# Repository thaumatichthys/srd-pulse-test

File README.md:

# Step Recovery Diode Pulse Generator

Note this thing hasn't been tested yet so all of this could just be stuff I dreamed up and might not work at all.

Unfortunately there seems to be only one step recovery diode (SRD) that is easily obtainable nowadays on Digikey or mouser. That being the MACOM MA144769-287T. 
This one is pretty mediocre compared to the high performance ones used in sampling heads etc, with a transition time of 150ps, around 1pF of capacitance, and it is a SOT-23 package which 
is pretty large and has a correspondingly huge package inductance. Therefore the performance of this pulse generator is not expected to be too crazy. Hopefully I can get sub 300ps pulses with
dv/dt of greater than maybe 10-20 mV/ps rise and fall time.

### SRD Drive

To get an SRD to "snap", you basically just run a forward current through it for a while, and it will build up an internal stored charge with the rate proportional to the amount of charge it has 
already. After it has a forward current running and some stored charge, you basically try to feed as much reverse current as possible, and it will basically start conducting using that stored charge.
After that runs out, it will abruptly stop conducting, and this impedance step is where the pulse comes from. This board uses the EPC21601 GaN eToF laser driver to do this. The EPC21601 seems to be pretty
good for this since it advertises <1ns fall time and was actually designed with timing accuracy in mind, unlike devices made for switching power supplies. It also has a gate driver built in and comes in a small
(read low inductance) package. Unfortunately that makes it kind of painful to assemble by hand.

### Stub Pulse Generator

The SRD circuit makes kind of a pulse with a fast rising edge and a slow RC-like falling edge. To speed up the falling edge, this board uses a ~16mm shorted 50 ohm stub. When the step forms, it goes down both the stub and towards the output, but the stub path has a reflection coefficient of gamma = -1, so the reflection will be negative. This negative reflection sums to hopefully close to zero, so the output will have a fast fall time too. This should all add together to roughly a 200-300ps pulse.

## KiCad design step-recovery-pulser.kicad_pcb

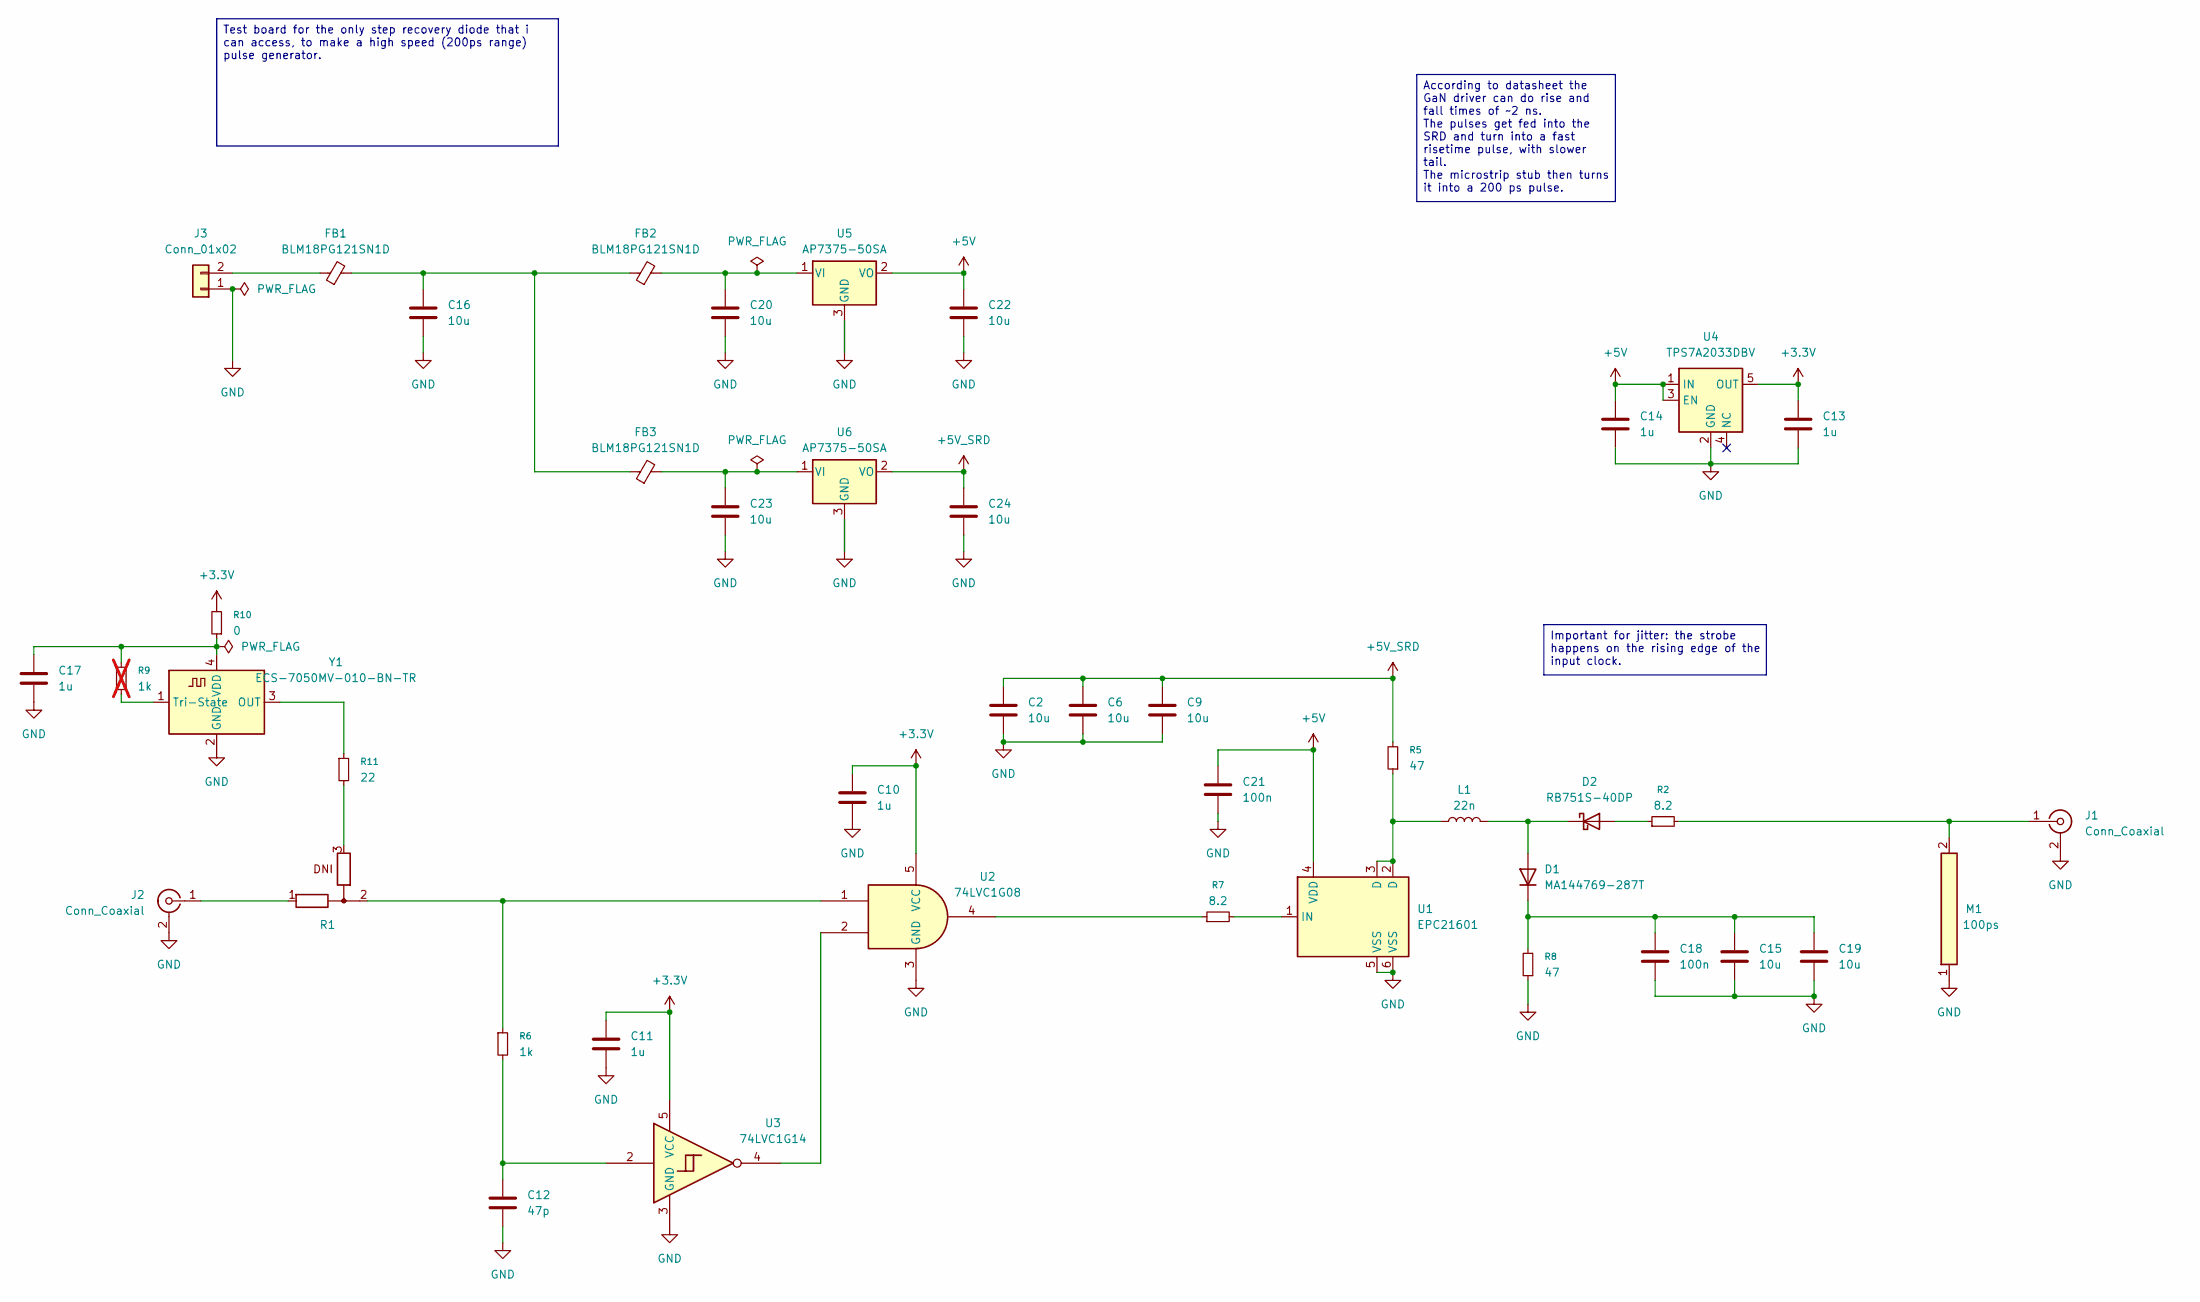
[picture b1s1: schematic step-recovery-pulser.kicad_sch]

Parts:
C2, C6, C9, C15, C16, C19, C20, C22, C23, C24: 10u; C_0805_2012Metric
C10, C11, C13, C14, C17: 1u; C_0402_1005Metric
C12: 47p; C_0402_1005Metric
C18, C21: 100n; C_0201_0603Metric
D1: MA144769-287T; SOT-23
D2: RB751S-40DP; D_0201_0603Metric
FB1, FB2, FB3: BLM18PG121SN1D; L_0603_1608Metric
J1, J2: Conn_Coaxial; ADAMTECH_RF2-143-T-17-50-G_IMPROVED
J3: Conn_01x02; PinHeader_1x02_P2.54mm_Vertical
L1: 22n; L_0402_1005Metric
M1: 100ps; MICROSTRIP_L17_W0.35
R1: R_0402_SELECT_MIRRORED
R2, R7: 8.2; R_0201_0603Metric
R5, R8: 47; R_0805_2012Metric
R6: 1k; R_0402_1005Metric
R9: 1k; R_0402_1005Metric; not fitted
R10: 0; R_0402_1005Metric
R11: 22; R_0402_1005Metric
U1: EPC21601; EPC_BGA-6_P0.5
U2: 74LVC1G08; SOT-353_SC-70-5
U3: 74LVC1G14; SOT-353_SC-70-5
U4: TPS7A2033DBV; SOT-23-5
U5, U6: AP7375-50SA; SOT-23
Y1: ECS-7050MV-010-BN-TR; Oscillator_SMD_IQD_IQXO70-4Pin_7.5x5.0mm_HandSoldering

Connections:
+3.3V: C10.1, C11.1, C13.1, R10.2, U2.5 (VCC), U3.5 (VCC), U4.5 (OUT)
+5V: C14.1, C21.1, C22.2, U1.4 (VDD), U4.1 (IN), U4.3 (EN), U5.2 (VO)
+5V_SRD: C2.2, C6.2, C9.2, C24.2, R5.2, U6.2 (VO)
GND: C2.1, C6.1, C9.1, C10.2, C11.2, C12.1, C13.2, C14.2, C15.1, C16.1, C17.2, C18.2, C19.1, C20.1, C21.2, C22.1, C23.1, C24.1, J1.2 (Ext), J2.2 (Ext), J3.1, M1.1, R8.1, U1.5 (VSS), U1.6 (VSS), U2.3 (GND), U3.3 (GND), U4.2 (GND), U5.3 (GND), U6.3 (GND), Y1.2 (GND)
unnamed: C12.2, R6.2, U3.2
unnamed: C16.2, FB1.2, FB2.1, FB3.1
unnamed: D1.1 (A), D2.1 (K), L1.2
unnamed: C15.2, C18.1, C19.2, D1.3 (K), R8.2
unnamed: D2.2 (A), R2.1
unnamed: J1.1 (In), M1.2, R2.2
unnamed: J2.1 (In), R1.1
unnamed: FB1.1, J3.2
unnamed: L1.1, R5.1, U1.2 (D), U1.3 (D)
unnamed: R1.2, R6.1, U2.1
unnamed: R1.3, R11.2
unnamed: R7.1, U2.4
unnamed: R7.2, U1.1 (IN)
unnamed: U2.2, U3.4
unnamed: C20.2, FB2.2, U5.1 (VI)
unnamed: C23.2, FB3.2, U6.1 (VI)
unnamed: R11.1, Y1.3 (OUT)
unnamed: R9.2, Y1.1 (Tri-State)
unnamed: C17.1, R9.1, R10.1, Y1.4 (VDD)

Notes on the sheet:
Test board for the only step recovery diode that i can access, to make a high speed (200ps range) pulse generator.
According to datasheet the GaN driver can do rise and fall times of ~2 ns. The pulses get fed into the SRD and turn into a fast risetime pulse, with slower tail. The microstrip stub then turns it into a 200 ps pulse.
Important for jitter: the strobe happens on the rising edge of the input clock.

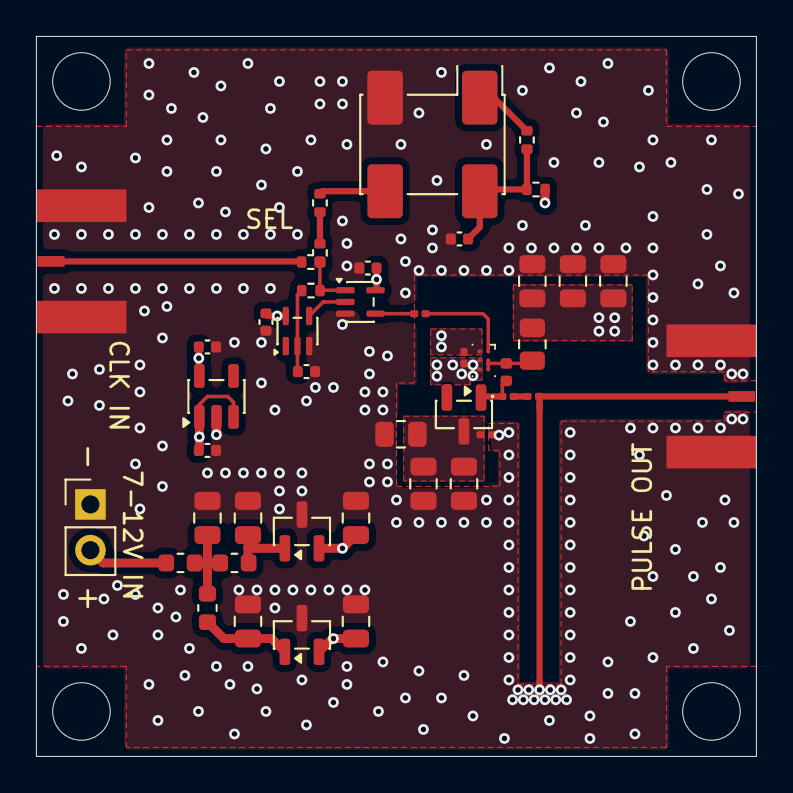
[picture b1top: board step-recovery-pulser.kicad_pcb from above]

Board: 4 copper layers, 40.0 x 40.0 mm, 44 parts (0 on the bottom side), 23 nets.
